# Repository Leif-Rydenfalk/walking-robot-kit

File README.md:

# Walking robot kit: electronics and control software

Open hardware and software for a small two-legged walking robot built on the
Arduino UNO Q. Fifteen Feetech bus servos on one TTL chain, a four-layer hat
that carries the camera, the audio, the distance sensor, the inertial sensor
and the servo bus, and a daemon on the board that owns the chain and serves a
live control page at 50 Hz.

Everything here is ours and is yours to use. The printed shell is not in this
release yet; see [What is not here](#what-is-not-here).

## What is in the box

| folder | what |
|---|---|
| `electronics/hat/` | the UNO Q hat: KiCad project, schematic, gerbers, BOM and pick-and-place, plus the Python that generates all of it |
| `electronics/imu-board/` | a small breakout for the body inertial sensor |
| `firmware/bus-bridge/` | the Arduino sketch that runs the servo chain on the MCU |
| `software/servo-bus/` | the Rust daemon that owns the bus and serves the control page |
| `software/tools/` | small Python tools: check supply voltage, record joint limits, hold a pose |
| `docs/` | wiring, servo IDs, and how to bring the robot up the first time |

## What you need

- An Arduino UNO Q (ABX00162). The Linux side runs the daemon, the MCU side runs the bus.
- Fifteen Feetech STS-protocol bus servos at 1 Mbit/s. We use the HD-1910-C001.
- The hat from `electronics/hat/`, or a URT-2 adapter on D0/D1 if you only want to
  drive servos and skip the camera and audio.
- A battery between 5.0 V and 8.4 V with enough current for fifteen servos.
  Never a two-cell pack in series: 13 V burns every servo on the chain in seconds.
- A computer with Rust and either the board on your network or a USB cable.

## Build it

The hat is a four-layer board, 68.68 by 53.44 mm, ENIG. Send
`electronics/hat/fab/gerbers.zip` to any PCB maker, with `fab/bom.csv` and
`fab/cpl.csv` if you want it assembled. `electronics/hat/schematic.pdf` is the
circuit on paper. The KiCad 10 project is in `electronics/hat/kicad/` if you want
to change it, and `board.py`, `sch.py` and `hat_parts.py` are what generated it.

## Program it

Build the daemon for the board, on your computer:

    rustup target add aarch64-unknown-linux-gnu
    cargo install cargo-zigbuild                      # and install Zig
    cd software/servo-bus
    cargo zigbuild --release --target aarch64-unknown-linux-gnu

Then push the binary, the sketch and the service to the board:

    cd software
    BOARD=arduino@<board address> ./install.sh        # over the network
    ./install.sh --adb                                # or over USB

The sketch compiles and flashes on the board, which takes about a minute the
first time. Nothing moves: the daemon starts with torque untouched and only
reads the bus.

Try it without hardware first:

    cd software/servo-bus && cargo run --release -- --fake --port 8938

Then open <http://127.0.0.1:8938/>. The fake bus puts two servos on ID 1 so you
can see the duplicate-ID warning.

## Run it

Open `http://<board address>:8938/` on a phone or a computer. Every servo on the
chain shows up within two seconds: angle, load, current, temperature, supply
voltage, torque state and the angle limits it is clamped to. Add `?control` to
the URL for a position slider per servo.

Plug servos in one at a time to set their IDs. They all leave the factory at
ID 1. `docs/servos.md` has the ID map and what the page refuses to do.

`docs/running.md` is the first bring-up, in order: charge, power on, hold the
zero pose, check the inertial sensor, move one joint.

## What is not here

The printed shell. Our current parts were dimensioned from a third party's
simulation meshes, which are licensed for non-commercial use only, so we cannot
put them under an open licence. They are being redrawn from our own
measurements and will land here when that is done.

## Licence

The software, the firmware and the generator scripts are Apache-2.0
([LICENSE](LICENSE)). The board designs, the gerbers and the BOMs are
CC BY-SA 4.0 ([LICENSES/CC-BY-SA-4.0.txt](LICENSES/CC-BY-SA-4.0.txt)), because
the camera routing on the hat is copied from Arduino's own UNO Media Carrier,
which is share-alike.

Third-party work this builds on is credited in [NOTICE](NOTICE).

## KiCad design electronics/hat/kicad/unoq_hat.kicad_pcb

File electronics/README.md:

# Electronics

Two boards. The hat is the one that matters; the IMU breakout is a small extra.

## hat

A four-layer hat for the Arduino UNO Q, 68.68 by 53.44 mm, 1.6 mm, ENIG. It
sits under the UNO Q on the two 2x30 board-to-board connectors and carries
everything the robot needs that the UNO Q does not have.

| block | part | notes |
|---|---|---|
| camera | 22-pin 0.5 mm flex connector on CSI0 | takes an IMX219 module. The ten CSI0 tracks are Arduino's own, copied from the UNO Media Carrier and length matched by them |
| power in | 6-pin JST PH pack plug (3 contacts per pole, 6 A), reverse-polarity FET, then two paths | 5.0 to 8.4 V in. Above that the daemon refuses to torque anything |
| UNO Q supply | TPS61088 boost to 11.86 V into the UNO Q's own VIN (7-24 V) | rev C. The hat never touches the UNO Q's 5 V or USB VBUS |
| amplifier supply | PTC, TPS62933 buck to 5 V | feeds only the amplifier |
| servo bus | half-duplex TTL with automatic direction | one 3-pin plug, the chain daisy-chains from there. Serial1, D0 and D1, 1 Mbit/s |
| pack monitor | INA226 across a 5 mOhm shunt in the pack feed | pack voltage and current |
| inertial | LSM6DSV16X on the 3.3 V bus at 0x6B | six axes with on-chip fusion |
| distance | header for a VL53L5CX or VL53L8CX breakout | |
| audio out | PAM8302A | one speaker plug |
| microphone | the carrier's microphone circuit | |
| touch | one capacitive pad | for petting the head |
| foot contacts | two 2-pin plugs | a switch or an FSR to ground per foot |

Everything except the board-to-board headers and the camera connector sits on
the bottom side, so nothing fouls the UNO Q above it.

### Getting one made

Send `hat/fab/gerbers.zip` to a PCB maker. Four layers, 1.6 mm, ENIG. Smallest
via is 0.20 mm drill on a 0.40 mm pad (one, inside the IMU's LGA); the rest are
0.25/0.45. For assembled boards add `fab/bom.csv`
and `fab/cpl.csv`; the part numbers are LCSC.
The order, with options, price and checks: `../docs/PCB-ORDER-LEIF-2026-10-11.md`.
Checks behind it: `hat/checks/` and `hat/docs/` (footprints, strap pins, power
budget, BOM stock).

`hat/schematic.pdf` is the circuit. `hat/kicad/` is the KiCad 10 project.

### Changing it

The board is generated, not drawn by hand. `hat_parts.py` is the whole design:
every part, every net, every position. `sch.py` turns it into the schematic and
`board.py` into the copper. Edit `hat_parts.py` and regenerate; do not edit the
KiCad files and expect the change to survive.

The CSI0 tracks are the exception. They are Arduino's, they are length matched,
and `board.py` locks them so the autorouter cannot touch them.

## imu-board

A two-layer breakout for an inertial sensor on the body plate, for when you
want the sensor away from the head. Same files, same process.

If you do not want to make a board for this, an MPU-6050 module wired straight
to the UNO Q header works. See `../docs/wiring.md`.

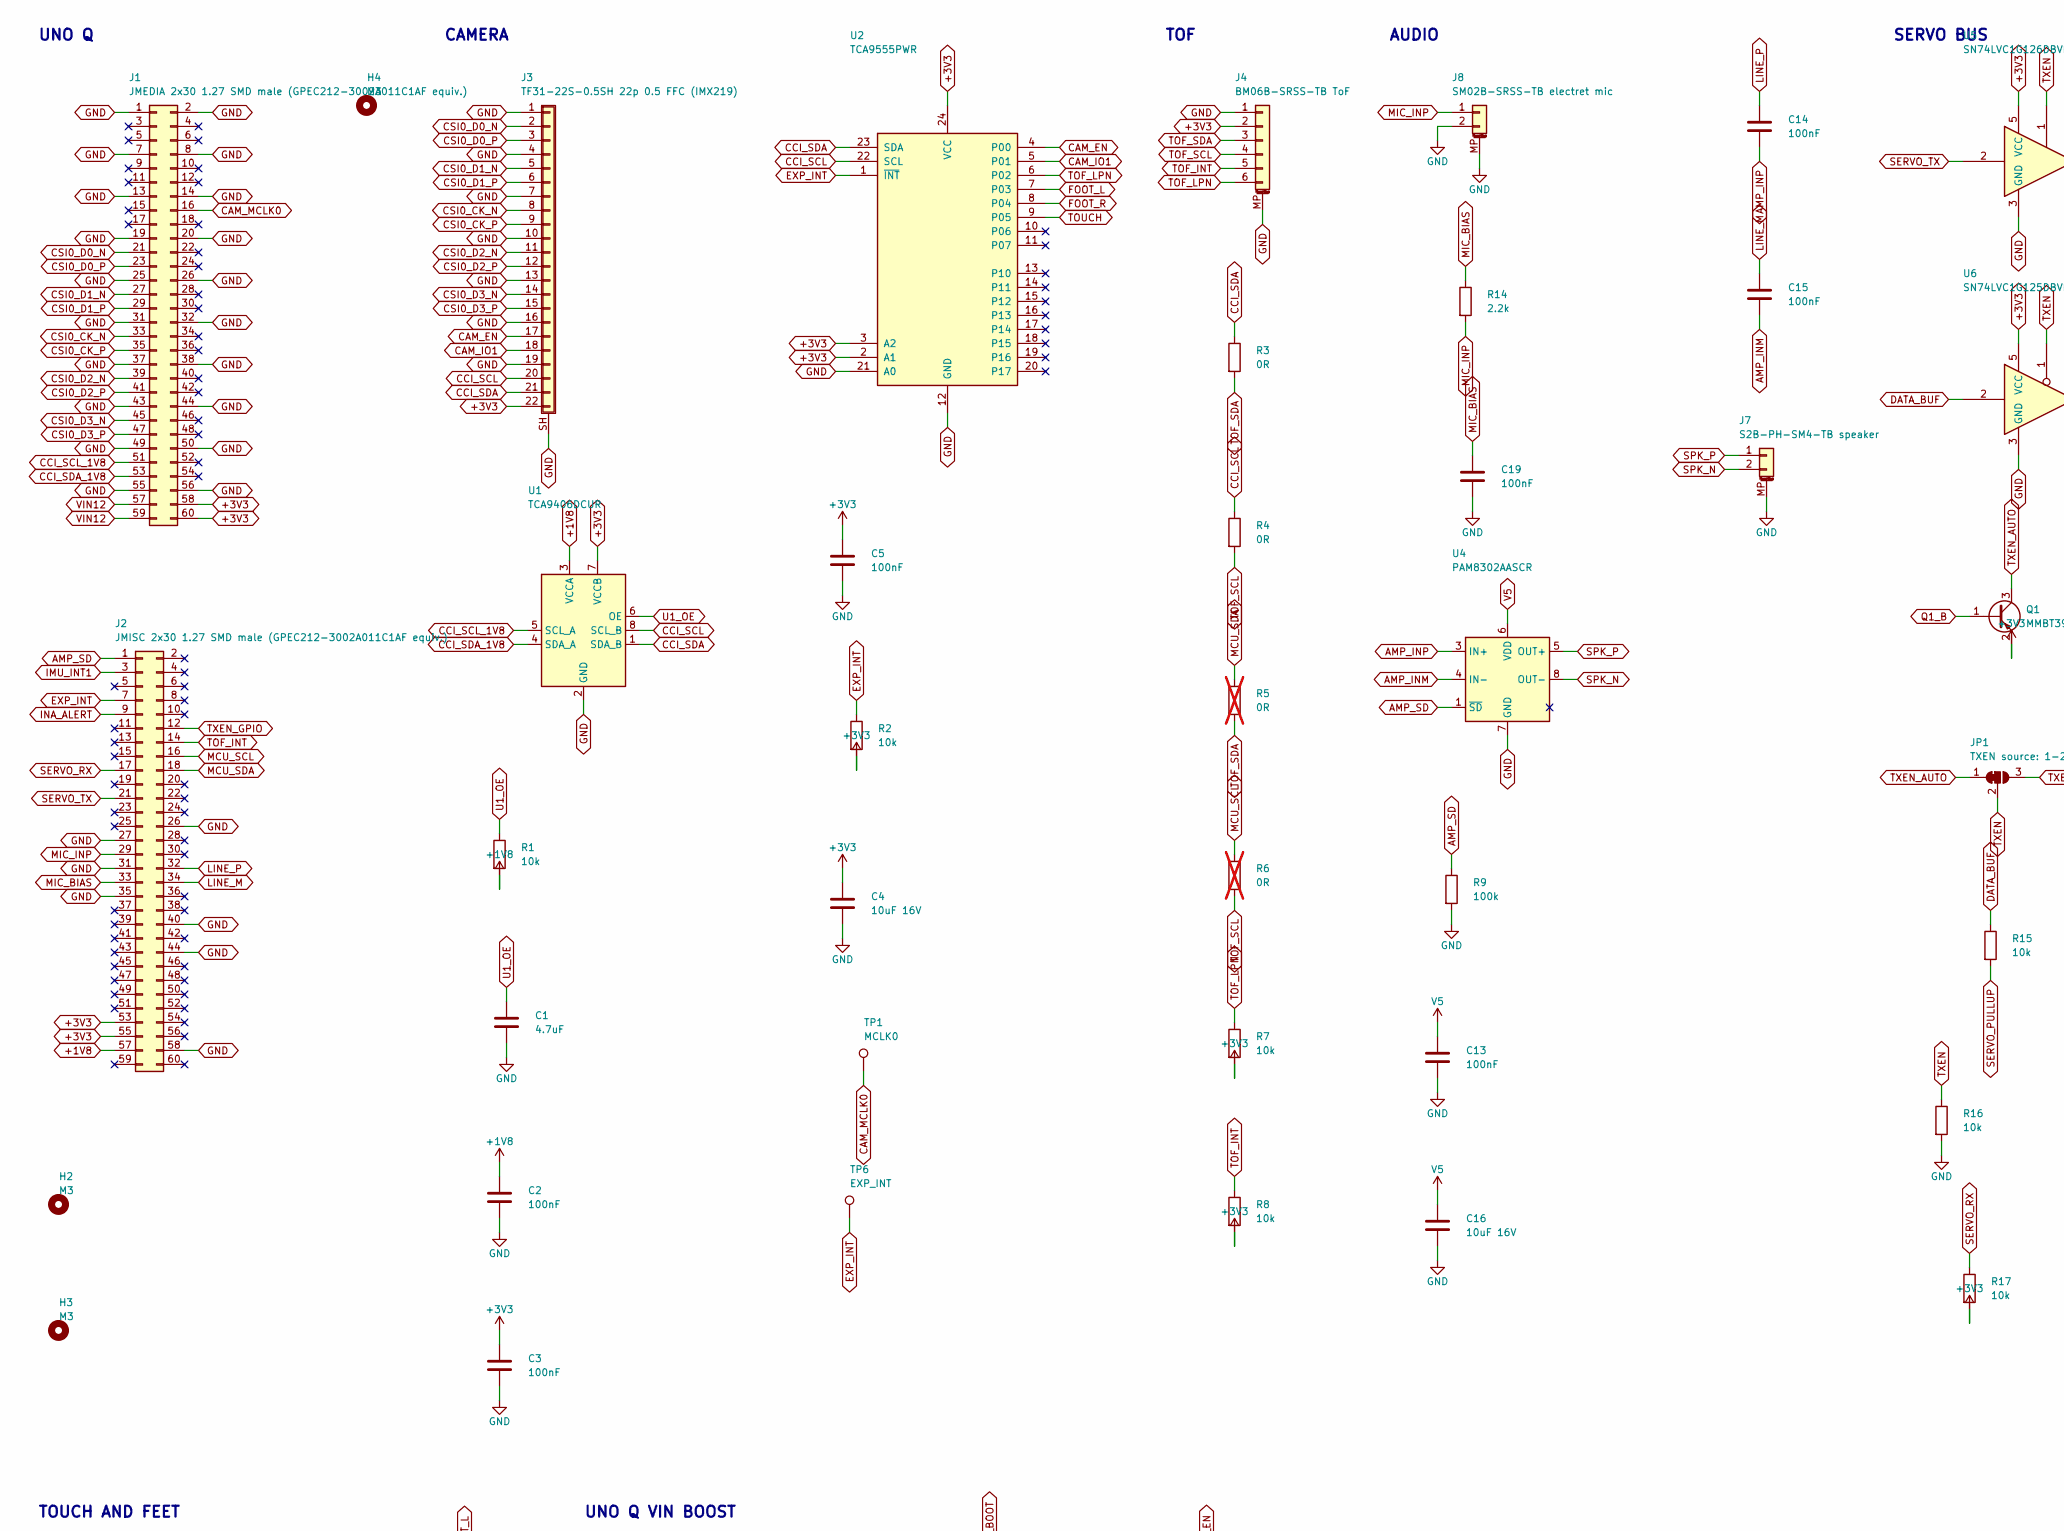
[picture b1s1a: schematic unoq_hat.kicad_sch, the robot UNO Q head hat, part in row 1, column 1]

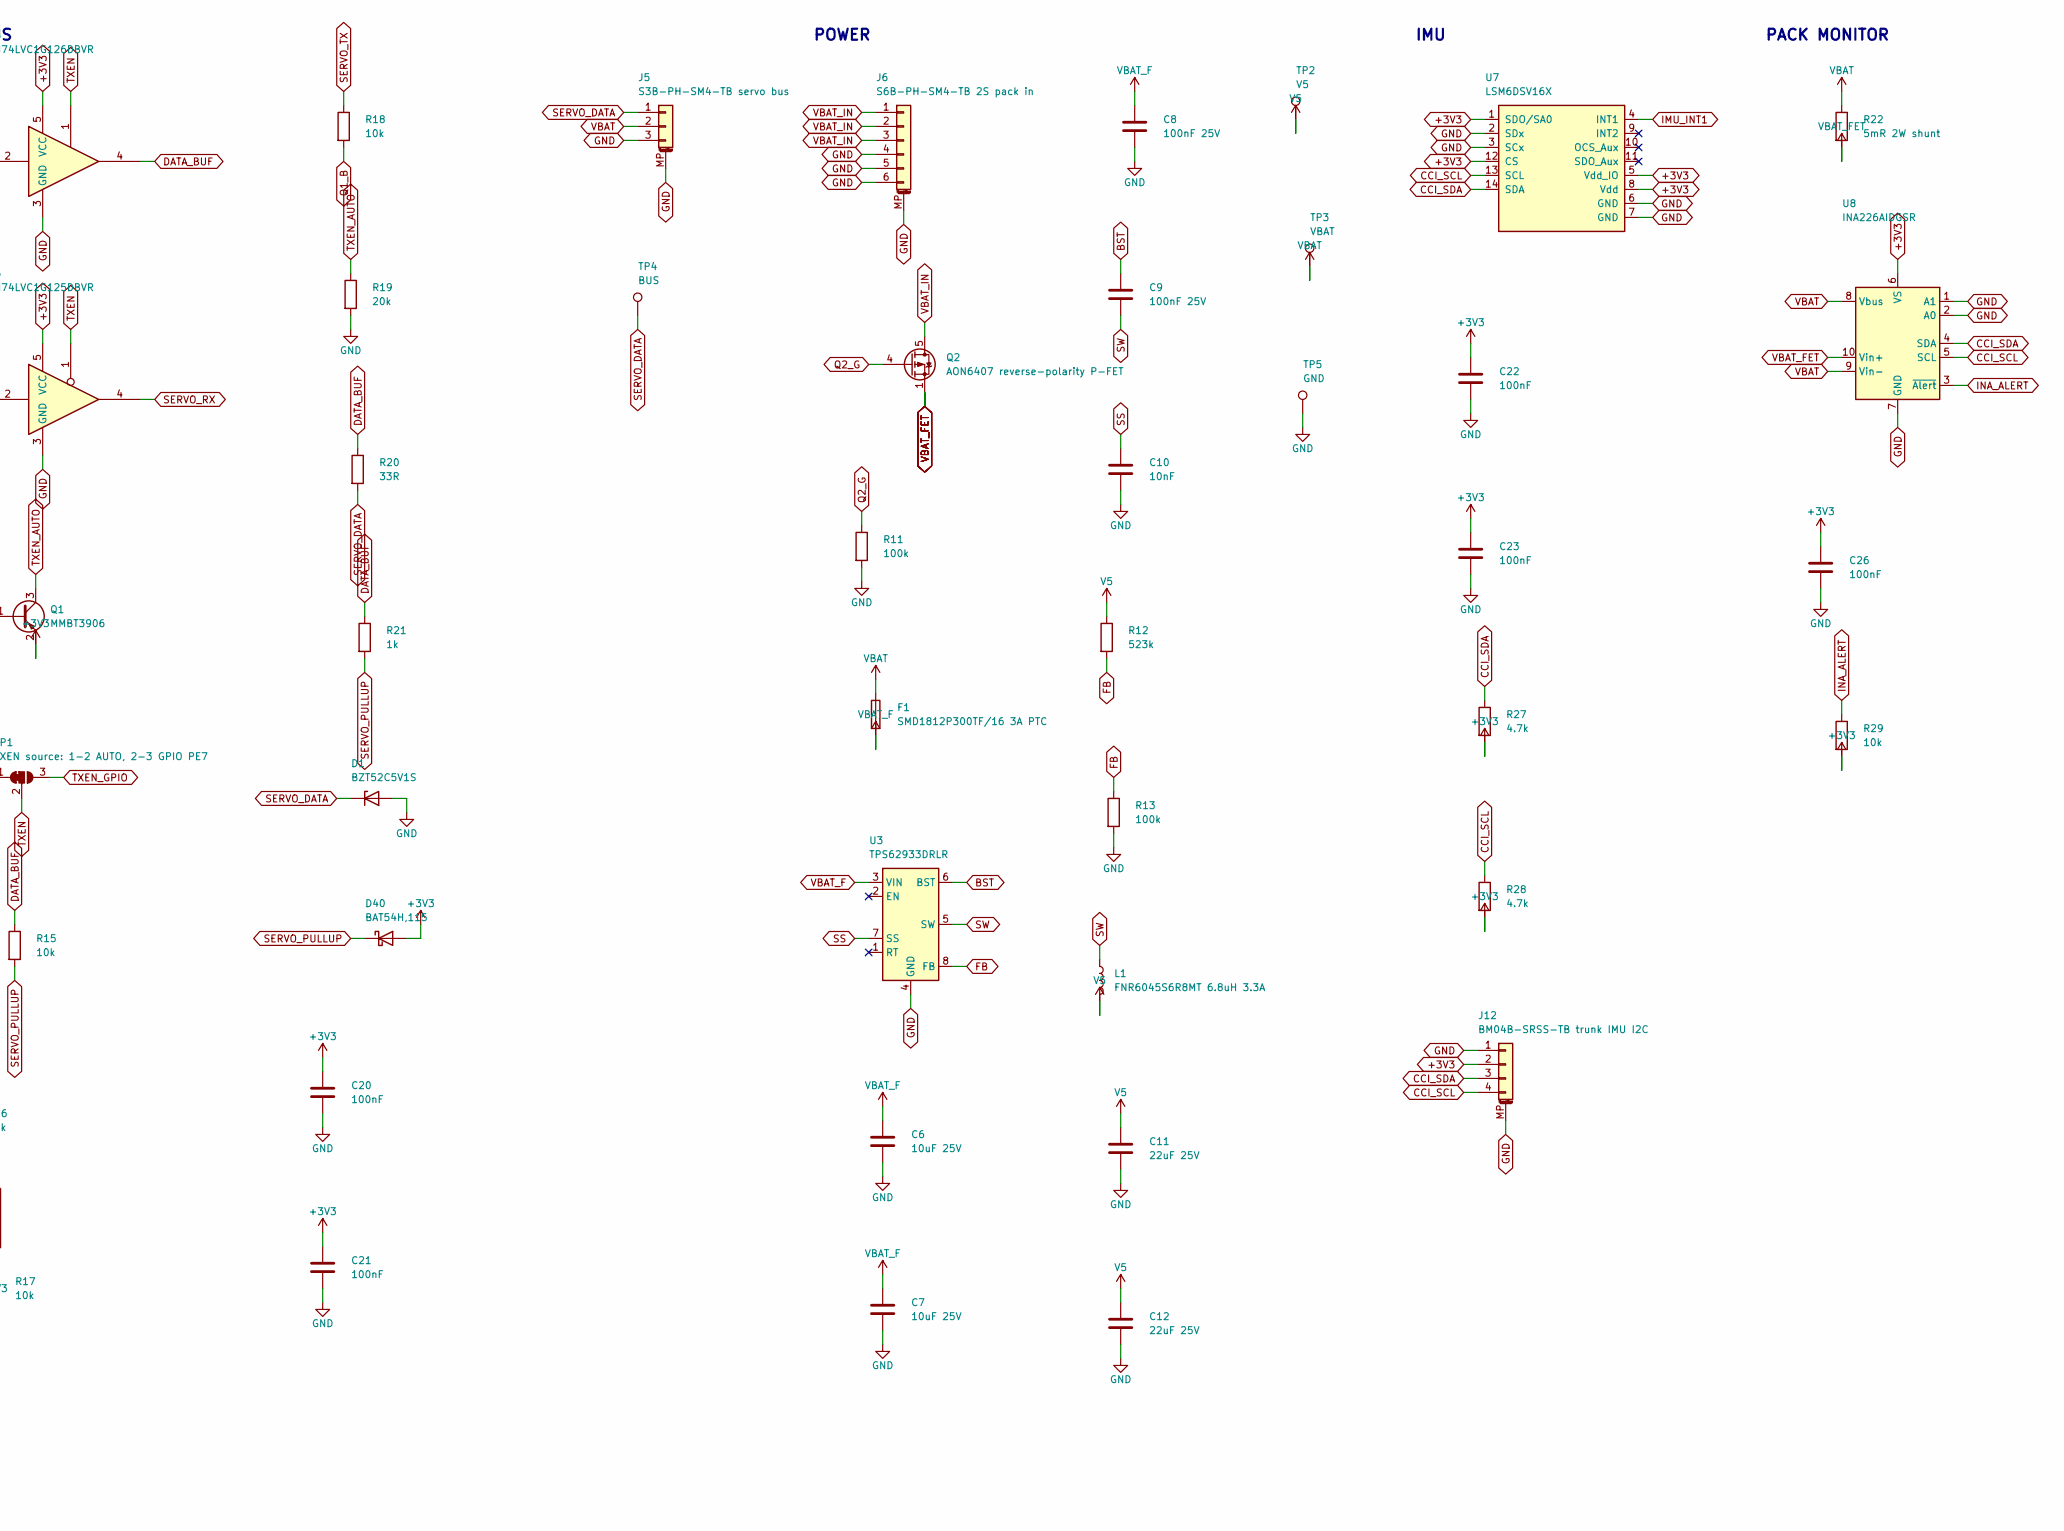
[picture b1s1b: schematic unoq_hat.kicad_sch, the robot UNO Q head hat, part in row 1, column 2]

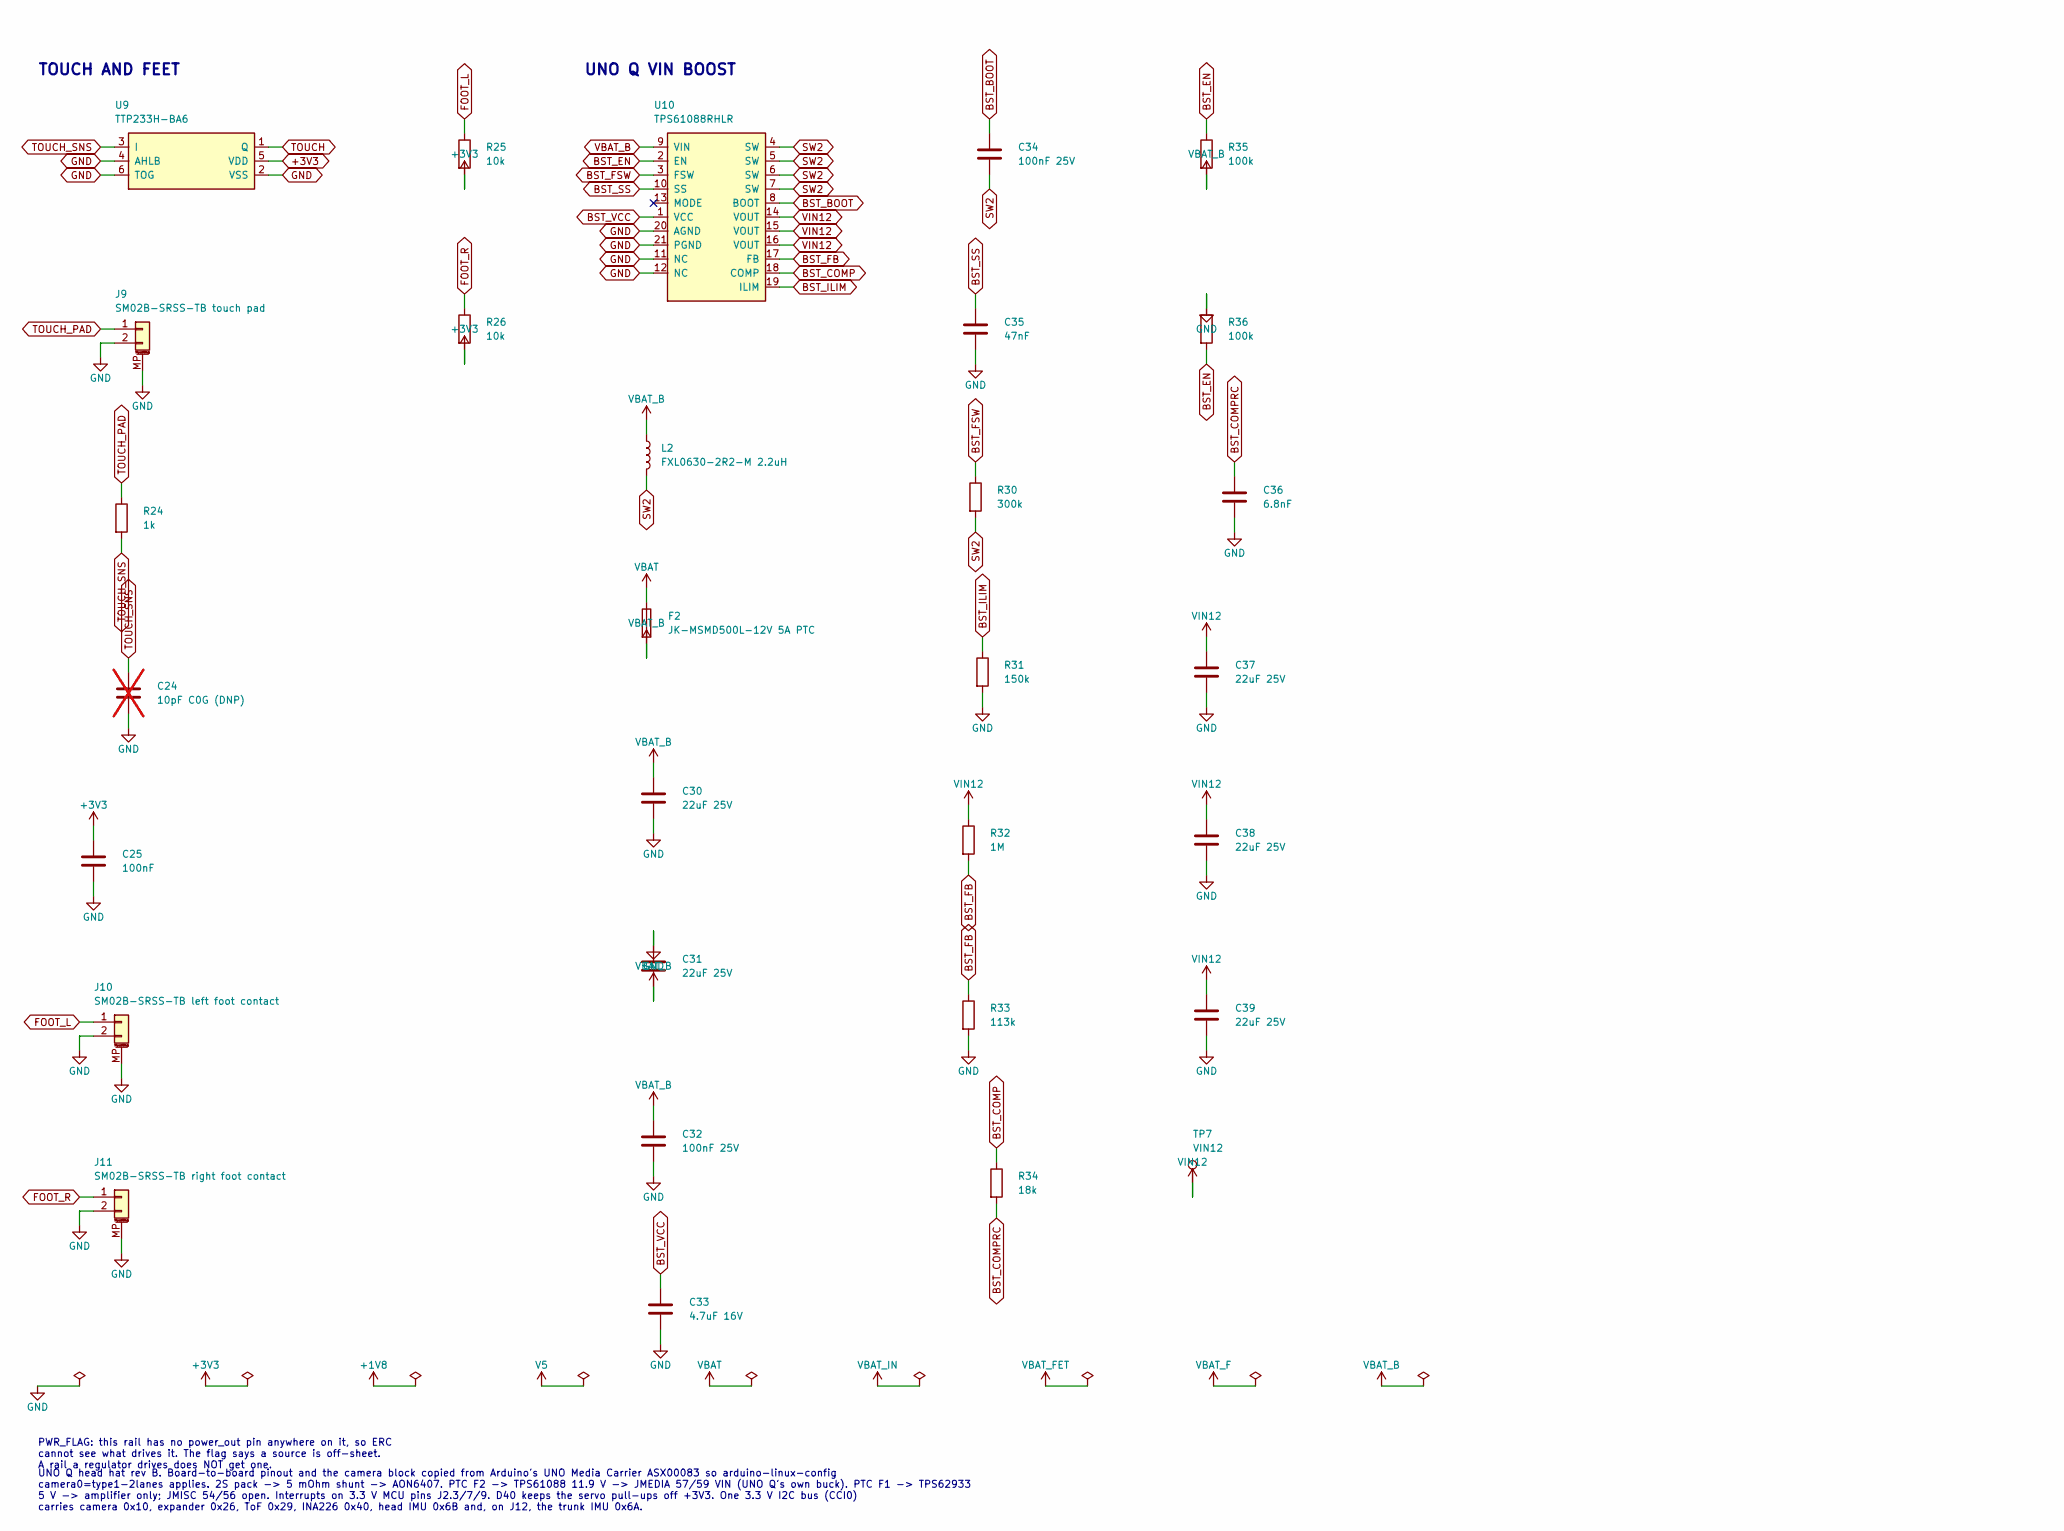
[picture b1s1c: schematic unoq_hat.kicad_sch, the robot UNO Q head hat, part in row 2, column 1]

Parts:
C1: 4.7uF; C_0402_1005Metric; LCSC Part # C23733
C2, C3, C5, C13, C14, C15, C19, C20, C21, C22, C23, C25, C26: 100nF; C_0402_1005Metric; LCSC Part # C1525
C4, C16: 10uF 16V; C_0805_2012Metric; LCSC Part # C1713
C6, C7: 10uF 25V; C_1206_3216Metric; LCSC Part # C77090
C8, C9, C32, C34: 100nF 25V; C_0402_1005Metric; LCSC Part # C105883
C10: 10nF; C_0402_1005Metric; LCSC Part # C60133
C11, C12, C30, C31, C37, C38, C39: 22uF 25V; C_1210_3225Metric; LCSC Part # C52306
C24: 10pF C0G (DNP); C_0402_1005Metric; not fitted
C33: 4.7uF 16V; C_0603_1608Metric; LCSC Part # C19666
C35: 47nF; C_0402_1005Metric; LCSC Part # C82219
C36: 6.8nF; C_0402_1005Metric; LCSC Part # C1542
D1: BZT52C5V1S; D_SOD-323; LCSC Part # C151348
D40: BAT54H,115; BAT54H_Nexperia_SOD123F; LCSC Part # C426769
F1: SMD1812P300TF/16 3A PTC; Fuse_1812_4532Metric; LCSC Part # C702820
F2: JK-MSMD500L-12V 5A PTC; Fuse_1812_4532Metric; LCSC Part # C2844238
H2, H3, H4: M3; MountingHole_3.2mm_M3
J1: JMEDIA 2x30 1.27 SMD male (GPEC212-3002A011C1AF e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; UNOQ_JMEDIA_2x30_P1.27_Male; LCSC Part # C191721
J2: JMISC 2x30 1.27 SMD male (GPEC212-3002A011C1AF eq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; UNOQ_JMEDIA_2x30_P1.27_Male; LCSC Part # C191721
J3: TF31-22S-0.5SH 22p 0.5 FFC (IMX219); FFC_22P_P0.5_TF31-22S; LCSC Part # C3169786
J4: BM06B-SRSS-TB ToF; JST_SH_BM06B-SRSS-TB_1x06-1MP_P1.00mm_Vertical; LCSC Part # C160392
J5: S3B-PH-SM4-TB servo bus; JST_PH_S3B-PH-SM4-TB_1x03-1MP_P2.00mm_Horizontal; LCSC Part # C265101
J6: S6B-PH-SM4-TB 2S pack in; JST_PH_S6B-PH-SM4-TB_1x06-1MP_P2.00mm_Horizontal; LCSC Part # C265405
J7: S2B-PH-SM4-TB speaker; JST_PH_S2B-PH-SM4-TB_1x02-1MP_P2.00mm_Horizontal; LCSC Part # C295747
J8: SM02B-SRSS-TB electret mic; JST_SH_SM02B-SRSS-TB_1x02-1MP_P1.00mm_Horizontal; LCSC Part # C160402
J9: SM02B-SRSS-TB touch pad; JST_SH_SM02B-SRSS-TB_1x02-1MP_P1.00mm_Horizontal; LCSC Part # C160402
J10: SM02B-SRSS-TB left foot contact; JST_SH_SM02B-SRSS-TB_1x02-1MP_P1.00mm_Horizontal; LCSC Part # C160402
J11: SM02B-SRSS-TB right foot contact; JST_SH_SM02B-SRSS-TB_1x02-1MP_P1.00mm_Horizontal; LCSC Part # C160402
J12: BM04B-SRSS-TB trunk IMU I2C; JST_SH_BM04B-SRSS-TB_1x04-1MP_P1.00mm_Vertical; LCSC Part # C160390
JP1: TXEN source: 1-2 AUTO, 2-3 GPIO PE7; SolderJumper-3_P1.3mm_Bridged12_RoundedPad1.0x1.5mm
L1: FNR6045S6R8MT 6.8uH 3.3A; FNR6045_6.0x6.0mm; LCSC Part # C168072
L2: FXL0630-2R2-M 2.2uH; L_Changjiang_FXL0630; LCSC Part # C167218
Q1: MMBT3906; SOT-23; LCSC Part # C727128
Q2: AON6407 reverse-polarity P-FET; PowerPAK_SO-8_Single; LCSC Part # C13899
R1, R2, R7, R8, R15, R16, R17, R18, R25, R26, R29: 10k; R_0402_1005Metric; LCSC Part # C25744
R3, R4: 0R; R_0402_1005Metric; LCSC Part # C17168
R5, R6: 0R; R_0402_1005Metric; LCSC Part # C17168; not fitted
R9, R11, R13, R35, R36: 100k; R_0402_1005Metric; LCSC Part # C25741
R12: 523k; R_0402_1005Metric; LCSC Part # C27011
R14: 2.2k; R_0402_1005Metric; LCSC Part # C25879
R19: 20k; R_0402_1005Metric; LCSC Part # C25765
R20: 33R; R_0402_1005Metric; LCSC Part # C138002
R21, R24: 1k; R_0402_1005Metric; LCSC Part # C106235
R22: 5mR 2W shunt; R_2512_6332Metric; LCSC Part # C185817
R27, R28: 4.7k; R_0402_1005Metric; LCSC Part # C25900
R30: 300k; R_0402_1005Metric; LCSC Part # C25774
R31: 150k; R_0402_1005Metric; LCSC Part # C25755
R32: 1M; R_0402_1005Metric; LCSC Part # C26083
R33: 113k; R_0402_1005Metric; LCSC Part # C25746
R34: 18k; R_0402_1005Metric; LCSC Part # C25762
TP1: MCLK0; TestPoint_Pad_D1.0mm
TP2: V5; TestPoint_Pad_D1.0mm
TP3: VBAT; TestPoint_Pad_D1.0mm
TP4: BUS; TestPoint_Pad_D1.0mm
TP5: GND; TestPoint_Pad_D1.0mm
TP6: EXP_INT; TestPoint_Pad_D1.0mm
TP7: VIN12; TestPoint_Pad_D1.0mm
U1: TCA9406DCUR; VSSOP-8_2.3x2mm_P0.5mm; LCSC Part # C840107
U2: TCA9555PWR; TSSOP-24_4.4x7.8mm_P0.65mm; LCSC Part # C465732
U3: TPS62933DRLR; SOT-583-8; LCSC Part # C3200405
U4: PAM8302AASCR; MSOP-8_3x3mm_P0.65mm; LCSC Part # C113367
U5: SN74LVC1G126DBVR; SOT-23-5; LCSC Part # C7834
U6: SN74LVC1G125DBVR; SOT-23-5; LCSC Part # C23654
U7: LSM6DSV16X; LGA-14_3x2.5mm_P0.5mm_LayoutBorder3x4y; LCSC Part # C5267406
U8: INA226AIDGSR; TSSOP-10_3x3mm_P0.5mm; LCSC Part # C49851
U9: TTP233H-BA6; SOT-23-6; LCSC Part # C2890349
U10: TPS61088RHLR; Texas_VQFN-RHL-20; LCSC Part # C87357

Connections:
AMP_INM: C15.2, U4.4 (IN-)
AMP_INP: C14.2, U4.3 (IN+)
AMP_SD: J2.1, R9.1, U4.1 (~SD)
BST: C9.1, U3.6 (BST)
BST_BOOT: C34.1, U10.8 (BOOT)
BST_COMP: R34.1, U10.18 (COMP)
BST_COMPRC: C36.1, R34.2
BST_EN: R35.1, R36.2, U10.2 (EN)
BST_FB: R32.2, R33.1, U10.17 (FB)
BST_FSW: R30.1, U10.3 (FSW)
BST_ILIM: R31.1, U10.19 (ILIM)
BST_SS: C35.1, U10.10 (SS)
BST_VCC: C33.1, U10.1 (VCC)
CAM_EN: J3.17, U2.4 (P00)
CAM_IO1: J3.18, U2.5 (P01)
CAM_MCLK0: J1.16, TP1.1
CCI_SCL: J3.20, J12.4, R4.1, R28.1, U1.8 (SCL_B), U2.22 (SCL), U7.13 (SCL), U8.5 (SCL)
CCI_SCL_1V8: J1.51, U1.5 (SCL_A)
CCI_SDA: J3.21, J12.3, R3.1, R27.1, U1.1 (SDA_B), U2.23 (SDA), U7.14 (SDA), U8.4 (SDA)
CCI_SDA_1V8: J1.53, U1.4 (SDA_A)
CSI0_CK_N: J1.33, J3.8
CSI0_CK_P: J1.35, J3.9
CSI0_D0_N: J1.21, J3.2
CSI0_D0_P: J1.23, J3.3
CSI0_D1_N: J1.27, J3.5
CSI0_D1_P: J1.29, J3.6
CSI0_D2_N: J1.39, J3.11
CSI0_D2_P: J1.41, J3.12
CSI0_D3_N: J1.45, J3.14
CSI0_D3_P: J1.47, J3.15
DATA_BUF: R15.1, R20.1, R21.1, U5.4, U6.2
EXP_INT: J2.7, R2.1, TP6.1, U2.1 (~INT)
FB: R12.2, R13.1, U3.8 (FB)
FOOT_L: J10.1, R25.1, U2.7 (P03)
FOOT_R: J11.1, R26.1, U2.8 (P04)
IMU_INT1: J2.3, U7.4 (INT1)
INA_ALERT: J2.9, R29.1, U8.3 (~Alert)
LINE_M: C15.1, J2.34
LINE_P: C14.1, J2.32
MCU_SCL: J2.16, R6.1
MCU_SDA: J2.18, R5.1
MIC_BIAS: C19.1, J2.33, R14.1
MIC_INP: J2.29, J8.1, R14.2
Q1_B: Q1.1 (B), R18.2
Q2_G: Q2.4 (G), R11.1
SERVO_DATA: D1.1 (K), J5.1, R20.2, TP4.1
SERVO_PULLUP: D40.1 (K), R15.2, R21.2
SERVO_RX: J2.17, R17.1, U6.4
SERVO_TX: J2.21, R18.1, U5.2
SPK_N: J7.2, U4.8 (OUT-)
SPK_P: J7.1, U4.5 (OUT+)
SS: C10.1, U3.7 (SS)
SW: C9.2, L1.1, U3.5 (SW)
SW2: C34.2, L2.2, R30.2, U10.4 (SW), U10.5 (SW), U10.6 (SW), U10.7 (SW)
TOF_INT: J2.14, J4.5, R8.1
TOF_LPN: J4.6, R7.1, U2.6 (P02)
TOF_SCL: J4.4, R4.2, R6.2
TOF_SDA: J4.3, R3.2, R5.2
TOUCH: U2.9 (P05), U9.1 (Q)
TOUCH_PAD: J9.1, R24.1
TOUCH_SNS: C24.1, R24.2, U9.3 (I)
TXEN: JP1.2 (C), R16.1, U5.1, U6.1
TXEN_AUTO: JP1.1 (A), Q1.3 (C), R19.1
TXEN_GPIO: J2.12, JP1.3 (B)
U1_OE: C1.1, R1.1, U1.6 (OE)
VBAT_IN: J6.1, J6.2, J6.3, Q2.5 (D)
VIN12: C37.1, C38.1, C39.1, J1.57, J1.59, R32.1, TP7.1, U10.14 (VOUT), U10.15 (VOUT), U10.16 (VOUT)

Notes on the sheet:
UNO Q
CAMERA
TOF
AUDIO
SERVO BUS
POWER
IMU
PACK MONITOR
TOUCH AND FEET
UNO Q VIN BOOST
PWR_FLAG: this rail has no power_out pin anywhere on it, so ERC cannot see what drives it. The flag says a source is off-sheet. A rail a regulator drives does NOT get one.
UNO Q head hat rev B. Board-to-board pinout and the camera block copied from Arduino's UNO Media Carrier ASX00083 so arduino-linux-config camera0=type1-2lanes applies. 2S pack -> 5 mOhm shunt -> AON6407. PTC F2 -> TPS61088 11.9 V -> JMEDIA 57/59 VIN (UNO Q's own buck). PTC F1 -> TPS62933 5 V -> amp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

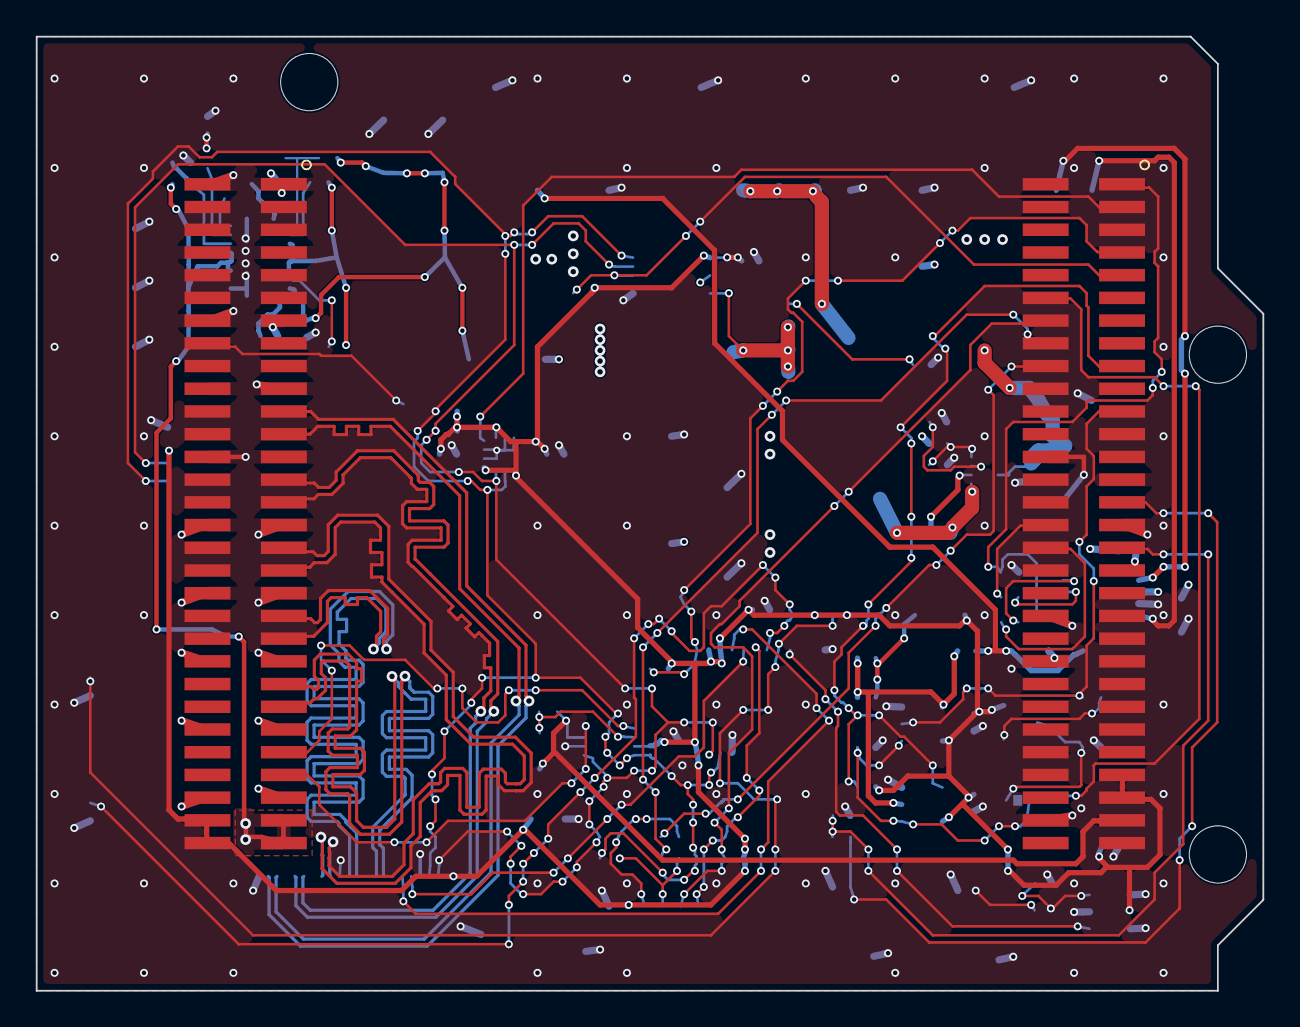
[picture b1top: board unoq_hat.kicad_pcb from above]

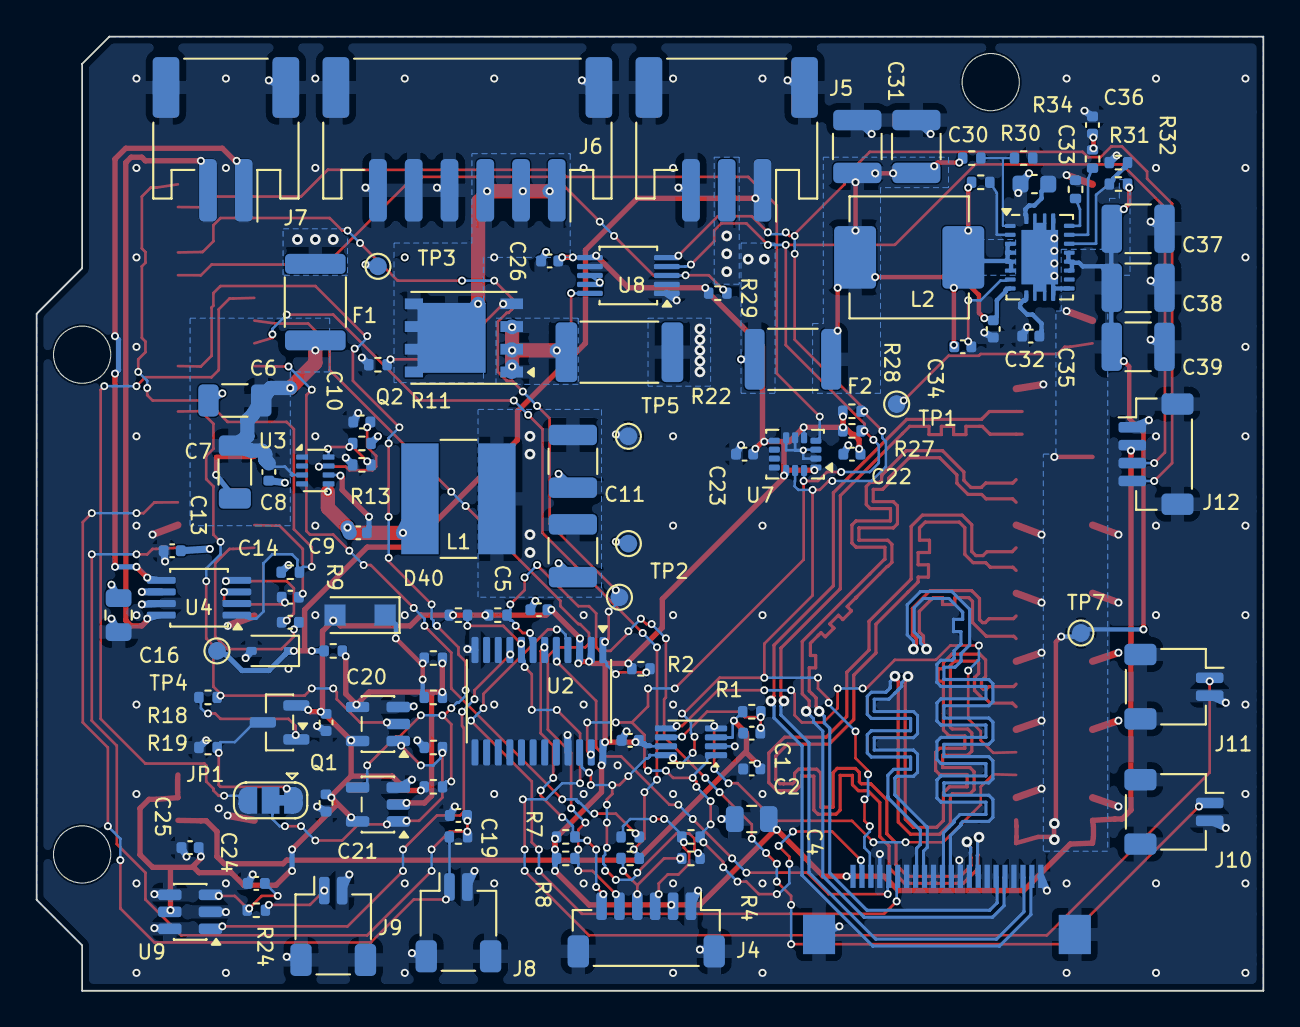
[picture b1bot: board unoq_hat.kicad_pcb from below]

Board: 4 copper layers, 68.6 x 53.3 mm, 109 parts (104 on the bottom side), 75 nets.

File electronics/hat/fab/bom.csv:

Comment,Designator,Footprint,LCSC Part #
4.7uF,C1,C_0402_1005Metric,C23733
10nF,C10,C_0402_1005Metric,C60133
22uF 25V,"C11,C12,C30,C31,C37,C38,C39",C_1210_3225Metric,C52306
100nF,"C2,C3,C5,C19,C20,C21,C13,C14,C15,C22,C23,C26,C25",C_0402_1005Metric,C1525
4.7uF 16V,C33,C_0603_1608Metric,C19666
47nF,C35,C_0402_1005Metric,C82219
6.8nF,C36,C_0402_1005Metric,C1542
10uF 16V,"C4,C16",C_0805_2012Metric,C1713
10uF 25V,"C6,C7",C_1206_3216Metric,C77090
100nF 25V,"C8,C9,C32,C34",C_0402_1005Metric,C105883
BZT52C5V1S,D1,D_SOD-323,C151348
"BAT54H,115",D40,BAT54H_Nexperia_SOD123F,C426769
SMD1812P300TF/16 3A PTC,F1,Fuse_1812_4532Metric,C702820
JK-MSMD500L-12V 5A PTC,F2,Fuse_1812_4532Metric,C2844238
JMEDIA 2x30 1.27 SMD male (GPEC212-3002A011C1AF equiv.),J1,UNOQ_JMEDIA_2x30_P1.27_Male,C191721
SM02B-SRSS-TB left foot contact,J10,JST_SH_SM02B-SRSS-TB_1x02-1MP_P1.00mm_Horizontal,C160402
SM02B-SRSS-TB right foot contact,J11,JST_SH_SM02B-SRSS-TB_1x02-1MP_P1.00mm_Horizontal,C160402
BM04B-SRSS-TB trunk IMU I2C,J12,JST_SH_BM04B-SRSS-TB_1x04-1MP_P1.00mm_Vertical,C160390
JMISC 2x30 1.27 SMD male (GPEC212-3002A011C1AF equiv.),J2,UNOQ_JMEDIA_2x30_P1.27_Male,C191721
TF31-22S-0.5SH 22p 0.5 FFC (IMX219),J3,FFC_22P_P0.5_TF31-22S,C3169786
BM06B-SRSS-TB ToF,J4,JST_SH_BM06B-SRSS-TB_1x06-1MP_P1.00mm_Vertical,C160392
S3B-PH-SM4-TB servo bus,J5,JST_PH_S3B-PH-SM4-TB_1x03-1MP_P2.00mm_Horizontal,C265101
S6B-PH-SM4-TB 2S pack in,J6,JST_PH_S6B-PH-SM4-TB_1x06-1MP_P2.00mm_Horizontal,C265405
S2B-PH-SM4-TB speaker,J7,JST_PH_S2B-PH-SM4-TB_1x02-1MP_P2.00mm_Horizontal,C295747
SM02B-SRSS-TB electret mic,J8,JST_SH_SM02B-SRSS-TB_1x02-1MP_P1.00mm_Horizontal,C160402
SM02B-SRSS-TB touch pad,J9,JST_SH_SM02B-SRSS-TB_1x02-1MP_P1.00mm_Horizontal,C160402
FNR6045S6R8MT 6.8uH 3.3A,L1,FNR6045_6.0x6.0mm,C168072
FXL0630-2R2-M 2.2uH,L2,L_Changjiang_FXL0630,C167218
MMBT3906,Q1,SOT-23,C727128
AON6407 reverse-polarity P-FET,Q2,PowerPAK_SO-8_Single,C13899
10k,"R1,R2,R7,R8,R15,R16,R17,R18,R29,R25,R26",R_0402_1005Metric,C25744
100k,"R11,R13,R9,R35,R36",R_0402_1005Metric,C25741
523k,R12,R_0402_1005Metric,C27011
2.2k,R14,R_0402_1005Metric,C25879
20k,R19,R_0402_1005Metric,C25765
33R,R20,R_0402_1005Metric,C138002
1k,"R21,R24",R_0402_1005Metric,C106235
5mR 2W shunt,R22,R_2512_6332Metric,C185817
4.7k,"R27,R28",R_0402_1005Metric,C25900
0R,"R3,R4",R_0402_1005Metric,C17168
300k,R30,R_0402_1005Metric,C25774
150k,R31,R_0402_1005Metric,C25755
1M,R32,R_0402_1005Metric,C26083
113k,R33,R_0402_1005Metric,C25746
18k,R34,R_0402_1005Metric,C25762
TCA9406DCUR,U1,VSSOP-8_2.3x2mm_P0.5mm,C840107
TPS61088RHLR,U10,Texas_VQFN-RHL-20,C87357
TCA9555PWR,U2,TSSOP-24_4.4x7.8mm_P0.65mm,C465732
TPS62933DRLR,U3,SOT-583-8,C3200405
PAM8302AASCR,U4,MSOP-8_3x3mm_P0.65mm,C113367
SN74LVC1G126DBVR,U5,SOT-23-5,C7834
SN74LVC1G125DBVR,U6,SOT-23-5,C23654
LSM6DSV16X,U7,LGA-14_3x2.5mm_P0.5mm_LayoutBorder3x4y,C5267406
INA226AIDGSR,U8,TSSOP-10_3x3mm_P0.5mm,C49851
TTP233H-BA6,U9,SOT-23-6,C2890349

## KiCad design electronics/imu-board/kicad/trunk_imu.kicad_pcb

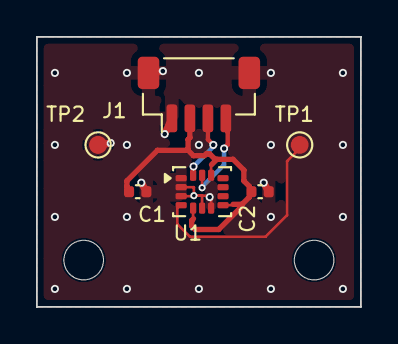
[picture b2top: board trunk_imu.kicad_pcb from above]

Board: 2 copper layers, 18.0 x 15.0 mm, 8 parts (0 on the bottom side), 5 nets.

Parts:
C1, C2: 100nF; C_0402_1005Metric
H1, H2: M2; MountingHole_2.2mm_M2
J1: BM04B-SRSS-TB I2C in; JST_SH_BM04B-SRSS-TB_1x04-1MP_P1.00mm_Vertical
TP1: INT1; TestPoint_Pad_D1.0mm
TP2: GND; TestPoint_Pad_D1.0mm
U1: LSM6DSV16X; LGA-14_3x2.5mm_P0.5mm_LayoutBorder3x4y

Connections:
+3V3: C1.1, C2.1, J1.2, U1.5, U1.8, U1.12
GND: C1.2, C2.2, J1.1, J1.MP, TP2.1, U1.1, U1.2, U1.3, U1.6, U1.7
IMU_INT1: TP1.1, U1.4
SCL: J1.4, U1.13
SDA: J1.3, U1.14

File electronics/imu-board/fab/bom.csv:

Comment,Designator,Footprint,LCSC Part #
100nF,"C1,C2",C_0402_1005Metric,C1525
BM04B-SRSS-TB I2C in,J1,JST_SH_BM04B-SRSS-TB_1x04-1MP_P1.00mm_Vertical,C160390
LSM6DSV16X,U1,LGA-14_3x2.5mm_P0.5mm_LayoutBorder3x4y,C5267406

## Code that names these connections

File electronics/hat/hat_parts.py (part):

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
Rev C (2026-10-10, foreman/microduck-assembly.60) fixes the three Rev B faults
found by the 2026-10-07 interface audit (HOLD.md):
  1. IMU_INT1, EXP_INT and INA_ALERT drove 3.3 V into 1.8 V SoC pins
     J2.37/39/41. They now land on MCU pins J2.3 PC7, J2.7 PC9, J2.9 PE4,
     3.3 V domain (datasheet ABX00162 sec. 9, JMISC table).
  2. The TPS62933 drove JMISC 54/56, which Arduino's schematic shows on USB
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     "C727128", "bottom", (55.0, 15.0), 0, True, "auto direction (Feetech HD-1910 p.7)"),
    ("JP1", "Jumper:SolderJumper_3_Bridged12",
     "Jumper:SolderJumper-3_P1.3mm_Bridged12_RoundedPad1.0x1.5mm",
     "TXEN source: 1-2 AUTO, 2-3 GPIO PE7", "", "bottom", (55.5, 10.5), 0, True,
     "ships bridged 1-2"),
    ("R15", "Device:R", R0402, "10k", "C25744", "bottom", (46.4, 16.4), 0, True, "bus pull-up"),
    ("R16", "Device:R", R0402, "10k", "C25744", "bottom", (46.4, 13.6), 0, True, "TXEN pull-down"),
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    # servo bus
    "SERVO_TX": ["J2.21", "U5.2", "R18.1"],
    "SERVO_RX": ["J2.17", "U6.4", "R17.1"],
    "TXEN_GPIO": ["J2.12", "JP1.3"],
    "TXEN": ["JP1.2", "U5.1", "U6.1", "R16.1"],
    "TXEN_AUTO": ["JP1.1", "Q1.3", "R19.1"],
    "Q1_B": ["Q1.1", "R18.2"],
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
# deliberately unconnected (drawn with a no-connect flag)
NC = (["U3.1", "U3.2", "U4.2"]                       # RT float = 500 kHz, EN float = on (TPS62933 table 7-1)
      # rev B: P03 P04 P05 (pins 7 8 9) are FOOT_L, FOOT_R and TOUCH
      + _p("U2", 10, 11, 13, 14, 15, 16, 17, 18, 19, 20)
      # LSM6DSV16X INT2 unused; OCS_Aux and SDO_Aux may be left open when the
      # auxiliary SPI is unused (DS13510 Table 2 note 3)
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
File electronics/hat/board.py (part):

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    for pin, dest, col in (("U10.17", "R32.2", 9.35), ("U10.18", "R34.1", 9.8),
                           ("U10.19", "R31.1", 10.25)):
        p, d = b.pad_xy(pin), b.pad_xy(dest)
        net = {"U10.17": "BST_FB", "U10.18": "BST_COMP", "U10.19": "BST_ILIM"}[pin]
        b.track(net, [p, (col, p[1]), (col, d[1] - 0.6 if d[1] > p[1] else d[1] + 0.6), d],
                width=0.15, layer="B.Cu")
        made.append("%s %s->%s col x %.2f" % (net, pin, dest, col))
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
